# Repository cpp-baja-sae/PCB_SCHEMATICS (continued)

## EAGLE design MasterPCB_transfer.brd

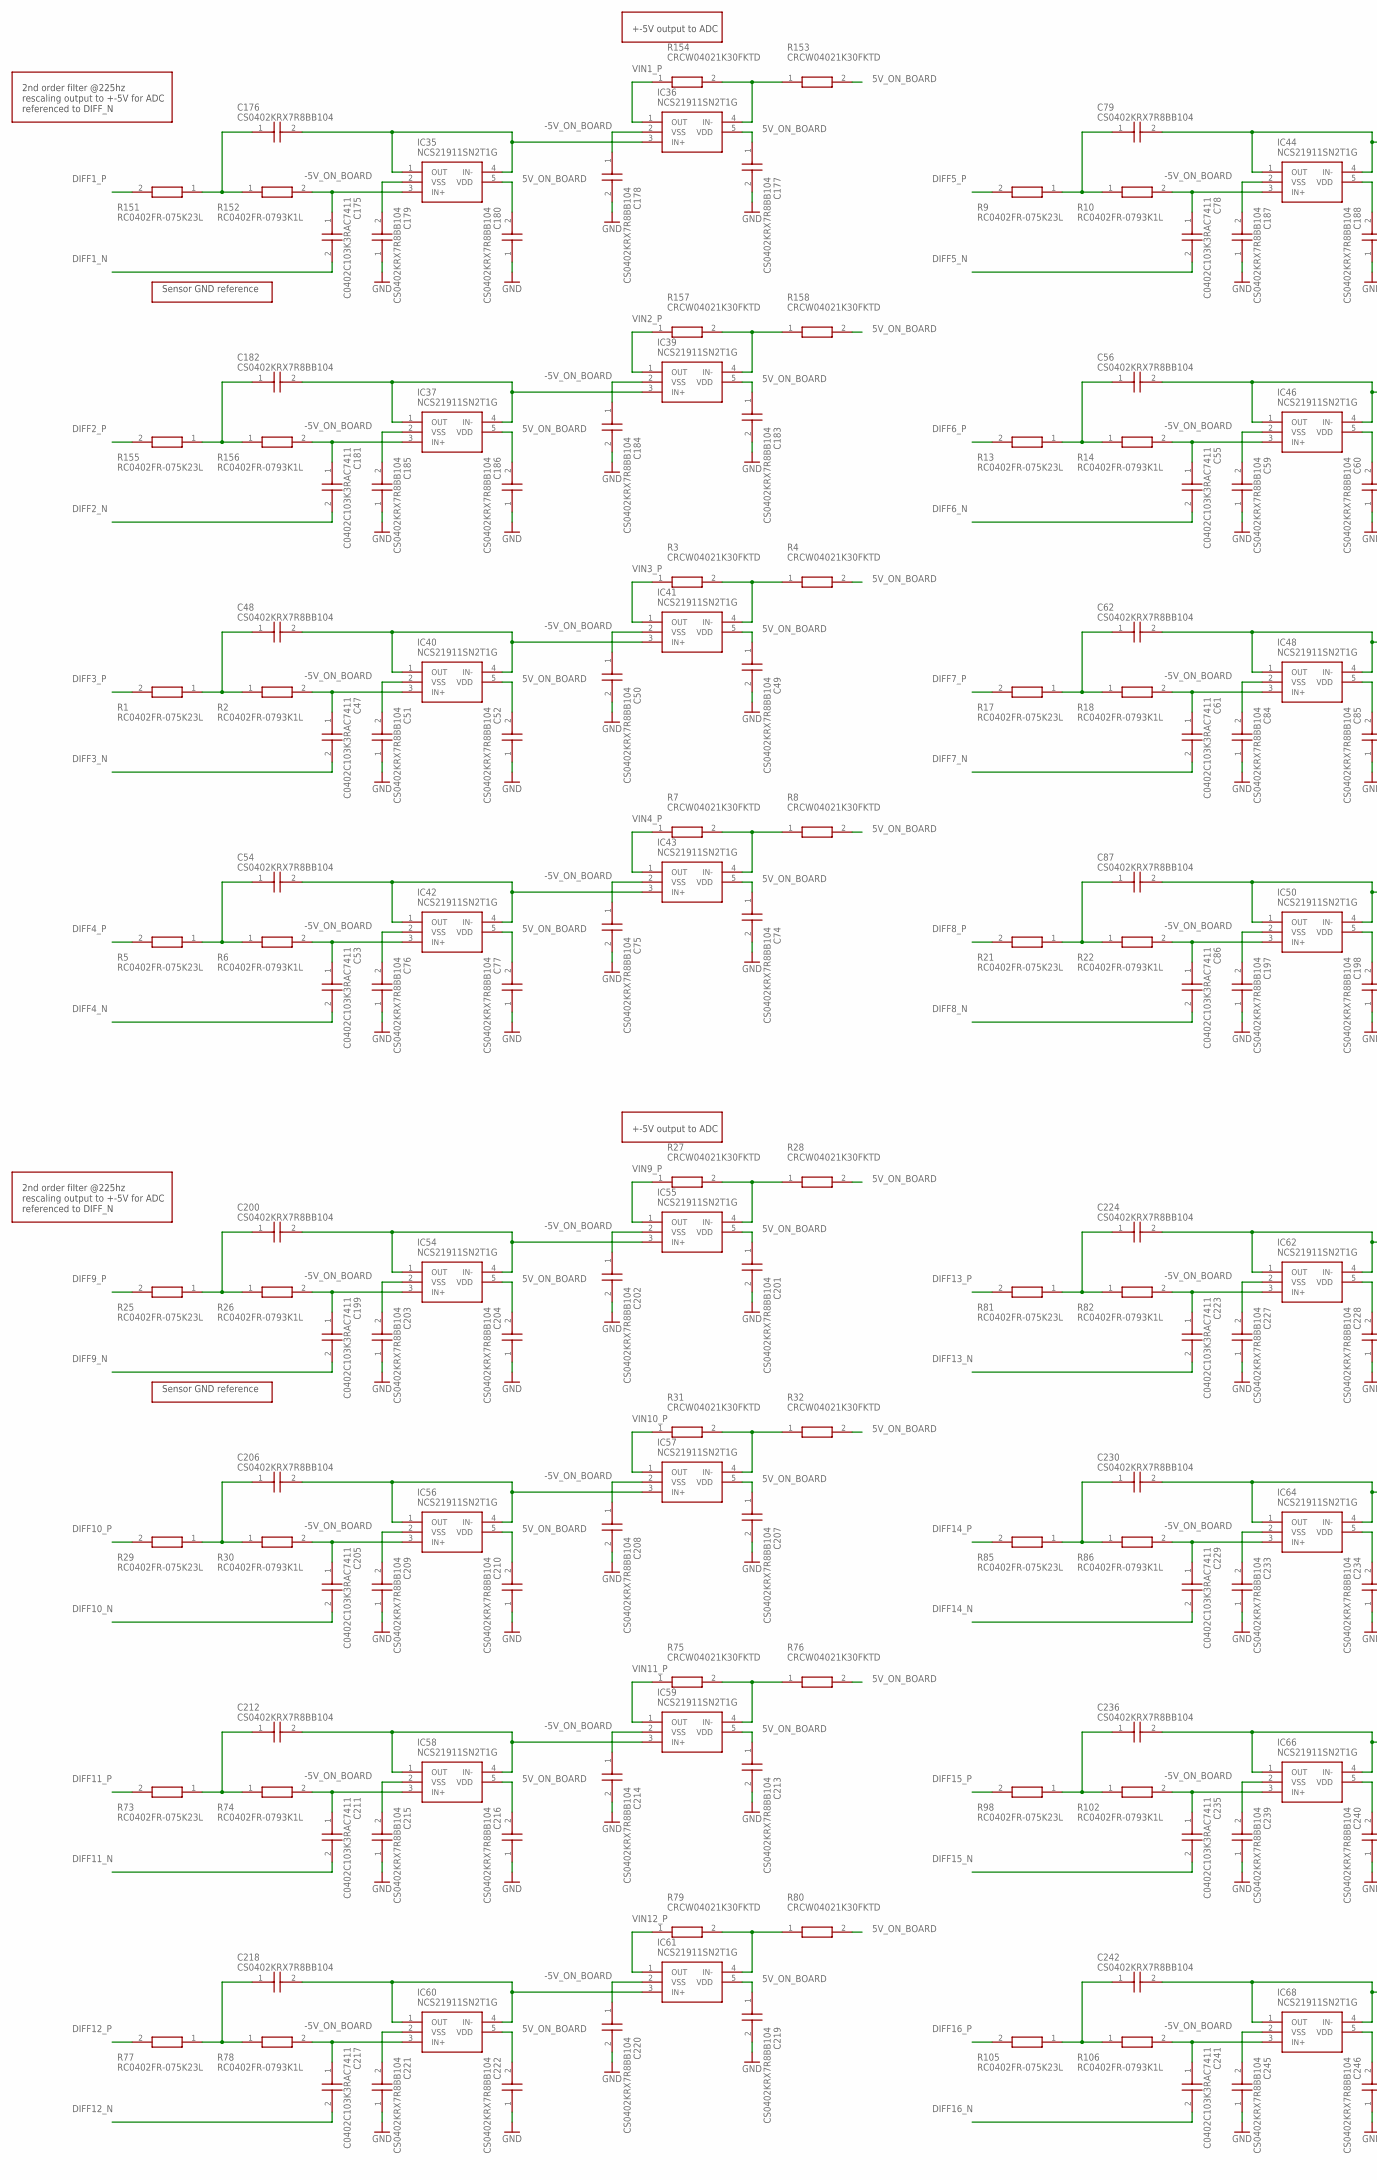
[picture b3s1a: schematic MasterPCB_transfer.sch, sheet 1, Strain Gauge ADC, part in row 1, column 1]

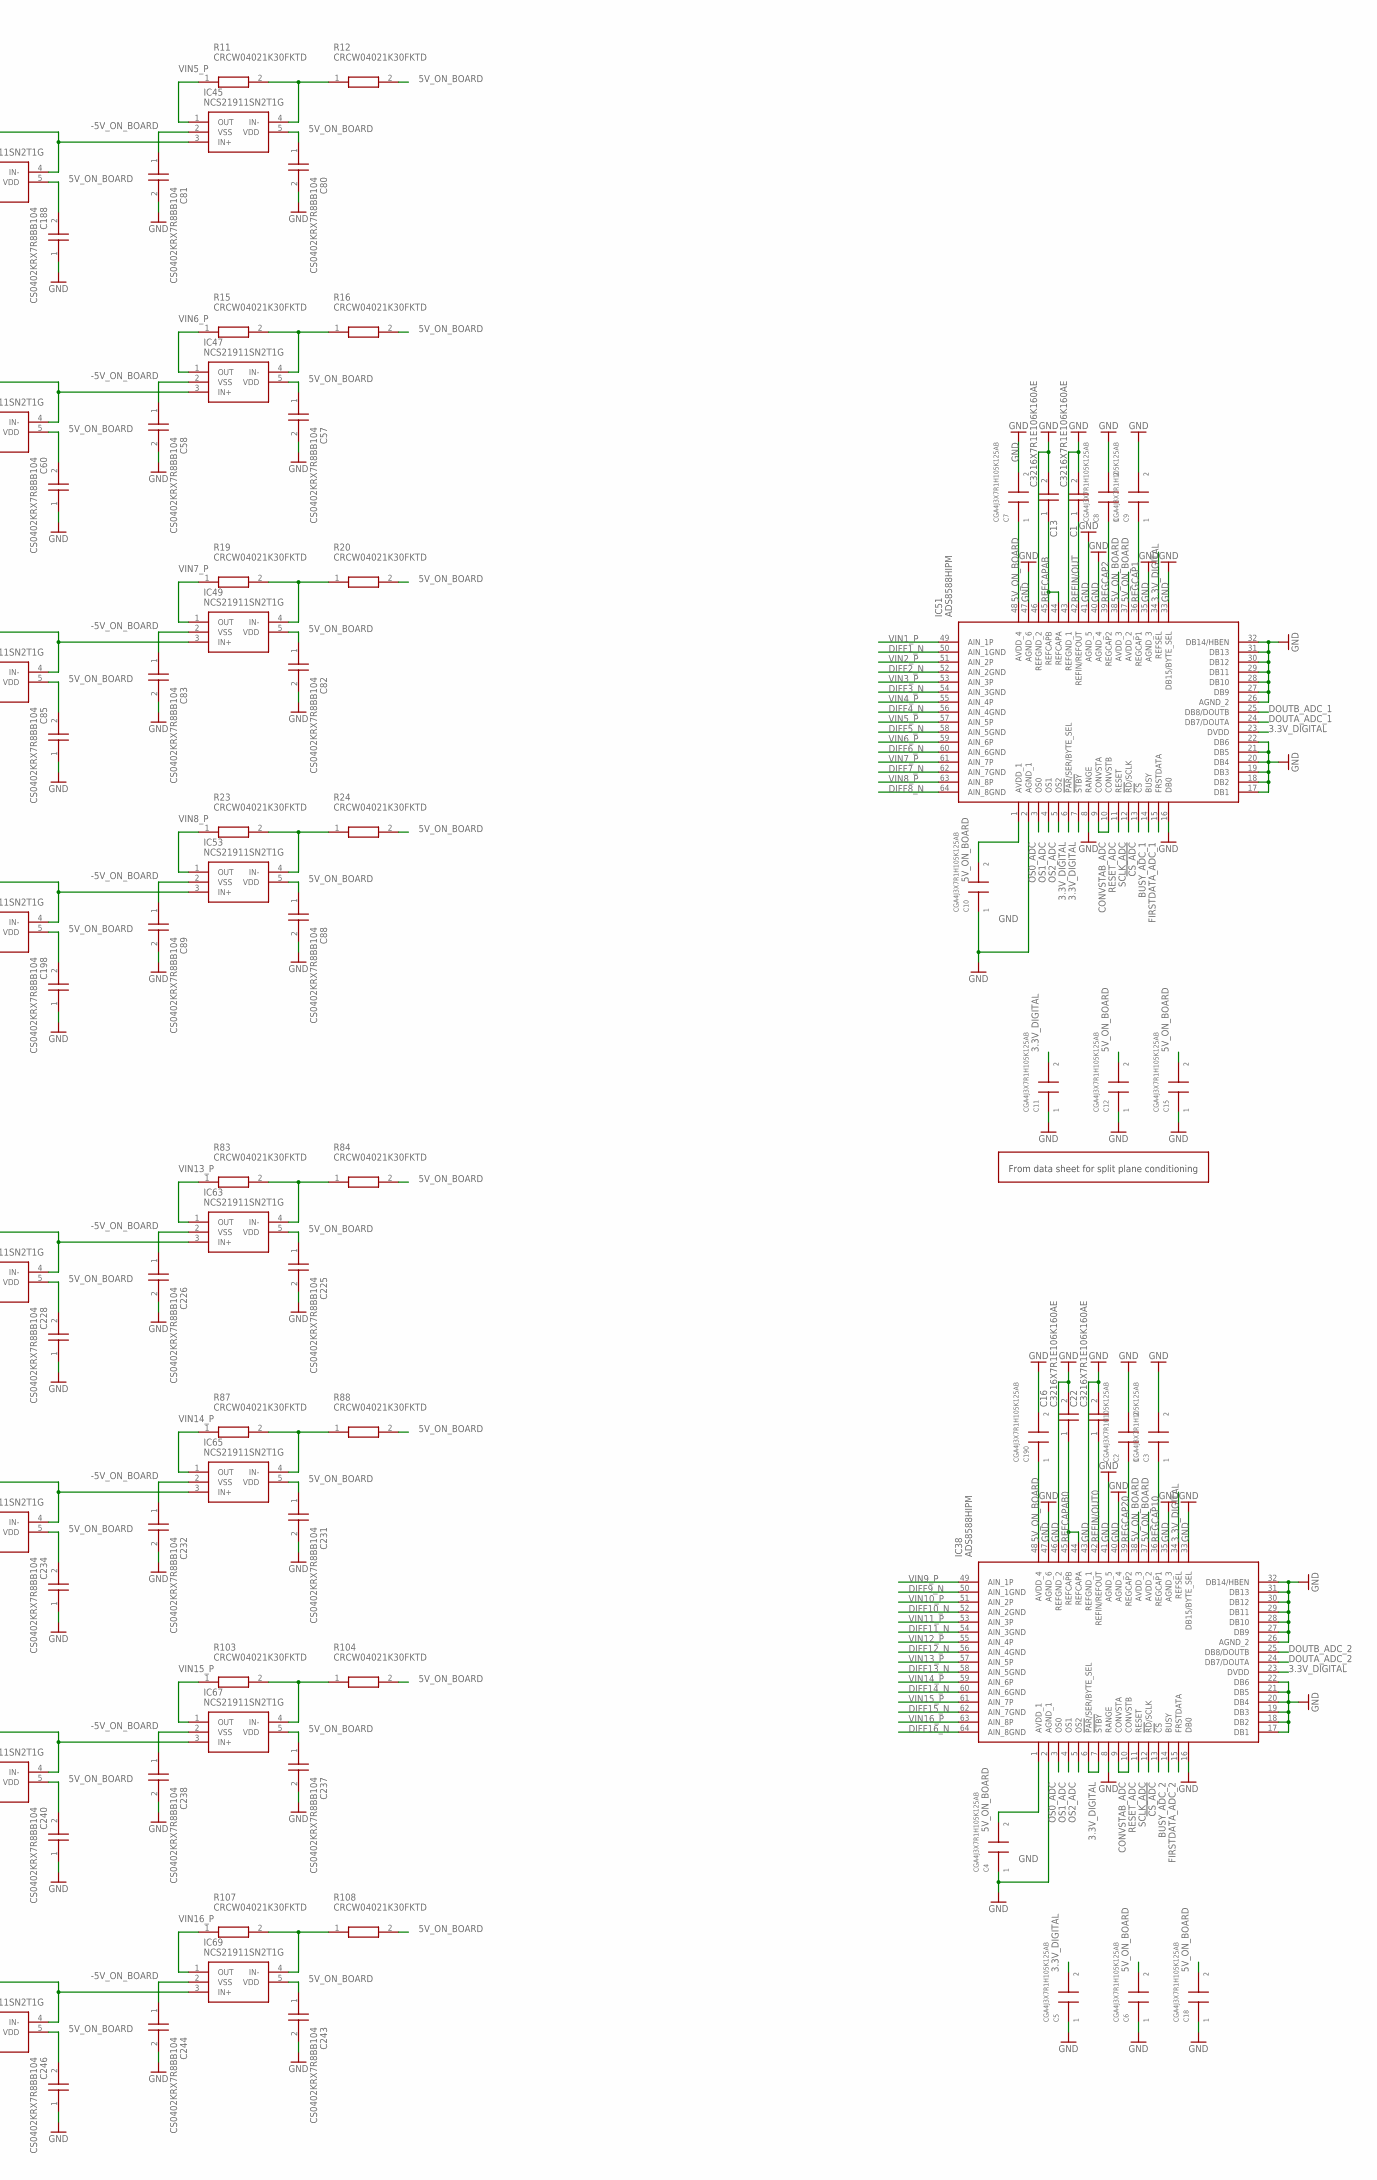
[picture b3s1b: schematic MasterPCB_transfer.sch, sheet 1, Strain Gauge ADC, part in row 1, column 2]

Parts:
C1, C13, C16, C22: C3216X7R1E106K160AE; C3216_COMMERCIAL
C2, C3, C4, C5, C6, C7, C8, C9, C10, C11, C12, C15, C18, C190: CGA4J3X7R1H105K125AB; CAPC2012X145N
C47, C53, C55, C61, C78, C86, C175, C181, C199, C205, C211, C217, C223, C229, C235, C241: C0402C103K3RAC7411; C0402
C48, C49, C50, C51, C52, C54, C56, C57, C58, C59, C60, C62, C74, C75, C76, C77, C79, C80, C81, C82, C83, C84, C85, C87, C88, C89, C176, C177, C178, C179, C180, C182, C183, C184, C185, C186, C187, C188, C197, C198, C200, C201, C202, C203, C204, C206, C207, C208, C209, C210, C212, C213, C214, C215, C216, C218, C219, C220, C221, C222, C224, C225, C226, C227, C228, C230, C231, C232, C233, C234, C236, C237, C238, C239, C240, C242, C243, C244, C245, C246: CS0402KRX7R8BB104; CAPC1005X65N
IC35, IC36, IC37, IC39, IC40, IC41, IC42, IC43, IC44, IC45, IC46, IC47, IC48, IC49, IC50, IC53, IC54, IC55, IC56, IC57, IC58, IC59, IC60, IC61, IC62, IC63, IC64, IC65, IC66, IC67, IC68, IC69: NCS21911SN2T1G; SOT95P275X110-5N
IC38, IC51: ADS8588HIPM; QFP50P1200X1200X160-64N_NO_3D
R1, R5, R9, R13, R17, R21, R25, R29, R73, R77, R81, R85, R98, R105, R151, R155: RC0402FR-075K23L; RESC1005X40N
R2, R6, R10, R14, R18, R22, R26, R30, R74, R78, R82, R86, R102, R106, R152, R156: RC0402FR-0793K1L; RESC1005X40N
R3, R4, R7, R8, R11, R12, R15, R16, R19, R20, R23, R24, R27, R28, R31, R32, R75, R76, R79, R80, R83, R84, R87, R88, R103, R104, R107, R108, R153, R154, R157, R158: CRCW04021K30FKTD; RESC1005X40N

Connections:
3.3V_DIGITAL: C5.2, C11.2, IC38.6 (!PAR!/SER/BYTE_SEL), IC38.7 (!STBY), IC38.23 (DVDD), IC38.34 (REFSEL), IC51.6 (!PAR!/SER/BYTE_SEL), IC51.7 (!STBY), IC51.23 (DVDD), IC51.34 (REFSEL); also elsewhere on the board
5V_ON_BOARD: C4.2, C6.2, C7.1, C10.2, C12.2, C15.2, C18.2, C49.1, C52.2, C57.1, C60.2, C74.1, C77.2, C80.1, C82.1, C85.2, C88.1, C177.1, C180.2, C183.1, C186.2, C188.2, C190.1, C198.2, C201.1, C204.2, C207.1, C210.2, C213.1, C216.2, C219.1, C222.2, C225.1, C228.2, C231.1, C234.2, C237.1, C240.2, C243.1, C246.2, IC35.5 (VDD), IC36.5 (VDD), IC37.5 (VDD), IC38.1 (AVDD_1), IC38.37 (AVDD_2), IC38.38 (AVDD_3), IC38.48 (AVDD_4), IC39.5 (VDD), IC40.5 (VDD), IC41.5 (VDD), IC42.5 (VDD), IC43.5 (VDD), IC44.5 (VDD), IC45.5 (VDD), IC46.5 (VDD), IC47.5 (VDD), IC48.5 (VDD), IC49.5 (VDD), IC50.5 (VDD), IC51.1 (AVDD_1), IC51.37 (AVDD_2), IC51.38 (AVDD_3), IC51.48 (AVDD_4), IC53.5 (VDD), IC54.5 (VDD), IC55.5 (VDD), IC56.5 (VDD), IC57.5 (VDD), IC58.5 (VDD), IC59.5 (VDD), IC60.5 (VDD), IC61.5 (VDD), IC62.5 (VDD), IC63.5 (VDD), IC64.5 (VDD), IC65.5 (VDD), IC66.5 (VDD), IC67.5 (VDD), IC68.5 (VDD), IC69.5 (VDD), R4.2, R8.2, R12.2, R16.2, R20.2, R24.2, R28.2, R32.2, R76.2, R80.2, R84.2, R88.2, R104.2, R108.2, R153.2, R158.2; also elsewhere on the board
!CS_ADC: IC38.13 (!CS), IC51.13 (!CS); also elsewhere on the board
-5V_ON_BOARD: C50.1, C51.2, C58.1, C59.2, C75.1, C76.2, C81.1, C83.1, C84.2, C89.1, C178.1, C179.2, C184.1, C185.2, C187.2, C197.2, C202.1, C203.2, C208.1, C209.2, C214.1, C215.2, C220.1, C221.2, C226.1, C227.2, C232.1, C233.2, C238.1, C239.2, C244.1, C245.2, IC35.2 (VSS), IC36.2 (VSS), IC37.2 (VSS), IC39.2 (VSS), IC40.2 (VSS), IC41.2 (VSS), IC42.2 (VSS), IC43.2 (VSS), IC44.2 (VSS), IC45.2 (VSS), IC46.2 (VSS), IC47.2 (VSS), IC48.2 (VSS), IC49.2 (VSS), IC50.2 (VSS), IC53.2 (VSS), IC54.2 (VSS), IC55.2 (VSS), IC56.2 (VSS), IC57.2 (VSS), IC58.2 (VSS), IC59.2 (VSS), IC60.2 (VSS), IC61.2 (VSS), IC62.2 (VSS), IC63.2 (VSS), IC64.2 (VSS), IC65.2 (VSS), IC66.2 (VSS), IC67.2 (VSS), IC68.2 (VSS), IC69.2 (VSS); also elsewhere on the board
BUSY_ADC_1: IC51.14 (BUSY); also elsewhere on the board
BUSY_ADC_2: IC38.14 (BUSY); also elsewhere on the board
CONVSTAB_ADC: IC38.9 (CONVSTA), IC38.10 (CONVSTB), IC51.9 (CONVSTA), IC51.10 (CONVSTB); also elsewhere on the board
DIFF1_N: C175.2, IC51.50 (AIN_1GND); also elsewhere on the board
DIFF1_P: R151.2; also elsewhere on the board
DIFF2_N: C181.2, IC51.52 (AIN_2GND); also elsewhere on the board
DIFF2_P: R155.2; also elsewhere on the board
DIFF3_N: C47.2, IC51.54 (AIN_3GND); also elsewhere on the board
DIFF3_P: R1.2; also elsewhere on the board
DIFF4_N: C53.2, IC51.56 (AIN_4GND); also elsewhere on the board
DIFF4_P: R5.2; also elsewhere on the board
DIFF5_N: C78.2, IC51.58 (AIN_5GND); also elsewhere on the board
DIFF5_P: R9.2; also elsewhere on the board
DIFF6_N: C55.2, IC51.60 (AIN_6GND); also elsewhere on the board
DIFF6_P: R13.2; also elsewhere on the board
DIFF7_N: C61.2, IC51.62 (AIN_7GND); also elsewhere on the board
DIFF7_P: R17.2; also elsewhere on the board
DIFF8_N: C86.2, IC51.64 (AIN_8GND); also elsewhere on the board
DIFF8_P: R21.2; also elsewhere on the board
DIFF9_N: C199.2, IC38.50 (AIN_1GND); also elsewhere on the board
DIFF9_P: R25.2; also elsewhere on the board
DIFF10_N: C205.2, IC38.52 (AIN_2GND); also elsewhere on the board
DIFF10_P: R29.2; also elsewhere on the board
DIFF11_N: C211.2, IC38.54 (AIN_3GND); also elsewhere on the board
DIFF11_P: R73.2; also elsewhere on the board
DIFF12_N: C217.2, IC38.56 (AIN_4GND); also elsewhere on the board
DIFF12_P: R77.2; also elsewhere on the board
DIFF13_N: C223.2, IC38.58 (AIN_5GND); also elsewhere on the board
DIFF13_P: R81.2; also elsewhere on the board
DIFF14_N: C229.2, IC38.60 (AIN_6GND); also elsewhere on the board
DIFF14_P: R85.2; also elsewhere on the board
DIFF15_N: C235.2, IC38.62 (AIN_7GND); also elsewhere on the board
DIFF15_P: R98.2; also elsewhere on the board
DIFF16_N: C241.2, IC38.64 (AIN_8GND); also elsewhere on the board
DIFF16_P: R105.2; also elsewhere on the board
DOUTA_ADC_1: IC51.24 (DB7/DOUTA); also elsewhere on the board
DOUTA_ADC_2: IC38.24 (DB7/DOUTA); also elsewhere on the board
DOUTB_ADC_1: IC51.25 (DB8/DOUTB); also elsewhere on the board
DOUTB_ADC_2: IC38.25 (DB8/DOUTB); also elsewhere on the board
FIRSTDATA_ADC_1: IC51.15 (FRSTDATA); also elsewhere on the board
FIRSTDATA_ADC_2: IC38.15 (FRSTDATA); also elsewhere on the board
GND: C1.2, C2.2, C3.2, C4.1, C5.1, C6.1, C7.2, C8.2, C9.2, C10.1, C11.1, C12.1, C13.2, C15.1, C16.2, C18.1, C22.2, C49.2, C50.2, C51.1, C52.1, C57.2, C58.2, C59.1, C60.1, C74.2, C75.2, C76.1, C77.1, C80.2, C81.2, C82.2, C83.2, C84.1, C85.1, C88.2, C89.2, C177.2, C178.2, C179.1, C180.1, C183.2, C184.2, C185.1, C186.1, C187.1, C188.1, C190.2, C197.1, C198.1, C201.2, C202.2, C203.1, C204.1, C207.2, C208.2, C209.1, C210.1, C213.2, C214.2, C215.1, C216.1, C219.2, C220.2, C221.1, C222.1, C225.2, C226.2, C227.1, C228.1, C231.2, C232.2, C233.1, C234.1, C237.2, C238.2, C239.1, C240.1, C243.2, C244.2, C245.1, C246.1, IC38.2 (AGND_1), IC38.8 (RANGE), IC38.16 (DB0), IC38.17 (DB1), IC38.18 (DB2), IC38.19 (DB3), IC38.20 (DB4), IC38.21 (DB5), IC38.22 (DB6), IC38.26 (AGND_2), IC38.27 (DB9), IC38.28 (DB10), IC38.29 (DB11), IC38.30 (DB12), IC38.31 (DB13), IC38.32 (DB14/HBEN), IC38.33 (DB15/BYTE_SEL), IC38.35 (AGND_3), IC38.40 (AGND_4), IC38.41 (AGND_5), IC38.43 (REFGND_1), IC38.46 (REFGND_2), IC38.47 (AGND_6), IC51.2 (AGND_1), IC51.8 (RANGE), IC51.16 (DB0), IC51.17 (DB1), IC51.18 (DB2), IC51.19 (DB3), IC51.20 (DB4), IC51.21 (DB5), IC51.22 (DB6), IC51.26 (AGND_2), IC51.27 (DB9), IC51.28 (DB10), IC51.29 (DB11), IC51.30 (DB12), IC51.31 (DB13), IC51.32 (DB14/HBEN), IC51.33 (DB15/BYTE_SEL), IC51.35 (AGND_3), IC51.40 (AGND_4), IC51.41 (AGND_5), IC51.43 (REFGND_1), IC51.46 (REFGND_2), IC51.47 (AGND_6); also elsewhere on the board
unnamed: C48.1, R1.1, R2.1
unnamed: C47.1, IC40.3 (IN+), R2.2
unnamed: IC41.4 (IN-), R3.2, R4.1
unnamed: C48.2, IC40.1 (OUT), IC40.4 (IN-), IC41.3 (IN+)
unnamed: C182.1, R155.1, R156.1
unnamed: C54.1, R5.1, R6.1
unnamed: C53.1, IC42.3 (IN+), R6.2
unnamed: IC43.4 (IN-), R7.2, R8.1
unnamed: C54.2, IC42.1 (OUT), IC42.4 (IN-), IC43.3 (IN+)
unnamed: C79.1, R9.1, R10.1
unnamed: C78.1, IC44.3 (IN+), R10.2
unnamed: IC45.4 (IN-), R11.2, R12.1
unnamed: C79.2, IC44.1 (OUT), IC44.4 (IN-), IC45.3 (IN+)
unnamed: C56.1, R13.1, R14.1
unnamed: C55.1, IC46.3 (IN+), R14.2
unnamed: IC47.4 (IN-), R15.2, R16.1
unnamed: C56.2, IC46.1 (OUT), IC46.4 (IN-), IC47.3 (IN+)
unnamed: C62.1, R17.1, R18.1
unnamed: C61.1, IC48.3 (IN+), R18.2
unnamed: IC49.4 (IN-), R19.2, R20.1
unnamed: C62.2, IC48.1 (OUT), IC48.4 (IN-), IC49.3 (IN+)
unnamed: C87.1, R21.1, R22.1
unnamed: C86.1, IC50.3 (IN+), R22.2
unnamed: IC53.4 (IN-), R23.2, R24.1
unnamed: C87.2, IC50.1 (OUT), IC50.4 (IN-), IC53.3 (IN+)
unnamed: C200.1, R25.1, R26.1
unnamed: C199.1, IC54.3 (IN+), R26.2
unnamed: IC55.4 (IN-), R27.2, R28.1
unnamed: C200.2, IC54.1 (OUT), IC54.4 (IN-), IC55.3 (IN+)
unnamed: C206.1, R29.1, R30.1
unnamed: C176.2, IC35.1 (OUT), IC35.4 (IN-), IC36.3 (IN+)
unnamed: C176.1, R151.1, R152.1
unnamed: C175.1, IC35.3 (IN+), R152.2
unnamed: IC36.4 (IN-), R153.1, R154.2
unnamed: C181.1, IC37.3 (IN+), R156.2
unnamed: IC39.4 (IN-), R157.2, R158.1
unnamed: C182.2, IC37.1 (OUT), IC37.4 (IN-), IC39.3 (IN+)
unnamed: C205.1, IC56.3 (IN+), R30.2
unnamed: IC57.4 (IN-), R31.2, R32.1
unnamed: C206.2, IC56.1 (OUT), IC56.4 (IN-), IC57.3 (IN+)
unnamed: C212.1, R73.1, R74.1
unnamed: C211.1, IC58.3 (IN+), R74.2
unnamed: IC59.4 (IN-), R75.2, R76.1
unnamed: C212.2, IC58.1 (OUT), IC58.4 (IN-), IC59.3 (IN+)
unnamed: C218.1, R77.1, R78.1
unnamed: C217.1, IC60.3 (IN+), R78.2
unnamed: IC61.4 (IN-), R79.2, R80.1
unnamed: C218.2, IC60.1 (OUT), IC60.4 (IN-), IC61.3 (IN+)
unnamed: C224.1, R81.1, R82.1
unnamed: C223.1, IC62.3 (IN+), R82.2
unnamed: IC63.4 (IN-), R83.2, R84.1
unnamed: C224.2, IC62.1 (OUT), IC62.4 (IN-), IC63.3 (IN+)
unnamed: C230.1, R85.1, R86.1
unnamed: C229.1, IC64.3 (IN+), R86.2
unnamed: IC65.4 (IN-), R87.2, R88.1
unnamed: C230.2, IC64.1 (OUT), IC64.4 (IN-), IC65.3 (IN+)
unnamed: C236.1, R98.1, R102.1
unnamed: C235.1, IC66.3 (IN+), R102.2
unnamed: IC67.4 (IN-), R103.2, R104.1
unnamed: C236.2, IC66.1 (OUT), IC66.4 (IN-), IC67.3 (IN+)
unnamed: C242.1, R105.1, R106.1
unnamed: C241.1, IC68.3 (IN+), R106.2
unnamed: IC69.4 (IN-), R107.2, R108.1
unnamed: C242.2, IC68.1 (OUT), IC68.4 (IN-), IC69.3 (IN+)
OS0_ADC: IC38.3 (OS0), IC51.3 (OS0); also elsewhere on the board
OS1_ADC: IC38.4 (OS1), IC51.4 (OS1); also elsewhere on the board
OS2_ADC: IC38.5 (OS2), IC51.5 (OS2); also elsewhere on the board
REFCAPAB: C13.1, IC51.44 (REFCAPA), IC51.45 (REFCAPB)
REFCAPAB0: C16.1, IC38.44 (REFCAPA), IC38.45 (REFCAPB)
REFIN/OUT: C1.1, IC51.42 (REFIN/REFOUT)
REFIN/OUT0: C22.1, IC38.42 (REFIN/REFOUT)
REGCAP1: C9.1, IC51.36 (REGCAP1)
REGCAP2: C8.1, IC51.39 (REGCAP2)
REGCAP10: C3.1, IC38.36 (REGCAP1)
REGCAP20: C2.1, IC38.39 (REGCAP2)
RESET_ADC: IC38.11 (RESET), IC51.11 (RESET); also elsewhere on the board
SCLK_ADC: IC38.12 (!RD!/SCLK), IC51.12 (!RD!/SCLK); also elsewhere on the board
VIN1_P: IC36.1 (OUT), IC51.49 (AIN_1P), R154.1
VIN2_P: IC39.1 (OUT), IC51.51 (AIN_2P), R157.1
VIN3_P: IC41.1 (OUT), IC51.53 (AIN_3P), R3.1
VIN4_P: IC43.1 (OUT), IC51.55 (AIN_4P), R7.1
VIN5_P: IC45.1 (OUT), IC51.57 (AIN_5P), R11.1
VIN6_P: IC47.1 (OUT), IC51.59 (AIN_6P), R15.1
VIN7_P: IC49.1 (OUT), IC51.61 (AIN_7P), R19.1
VIN8_P: IC51.63 (AIN_8P), IC53.1 (OUT), R23.1
VIN9_P: IC38.49 (AIN_1P), IC55.1 (OUT), R27.1
VIN10_P: IC38.51 (AIN_2P), IC57.1 (OUT), R31.1
VIN11_P: IC38.53 (AIN_3P), IC59.1 (OUT), R75.1
VIN12_P: IC38.55 (AIN_4P), IC61.1 (OUT), R79.1
VIN13_P: IC38.57 (AIN_5P), IC63.1 (OUT), R83.1
VIN14_P: IC38.59 (AIN_6P), IC65.1 (OUT), R87.1
VIN15_P: IC38.61 (AIN_7P), IC67.1 (OUT), R103.1
VIN16_P: IC38.63 (AIN_8P), IC69.1 (OUT), R107.1

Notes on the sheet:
From data sheet for split plane conditioning
2nd order filter @225hz rescaling output to +-5V for ADC referenced to DIFF_N
Sensor GND reference
+-5V output to ADC

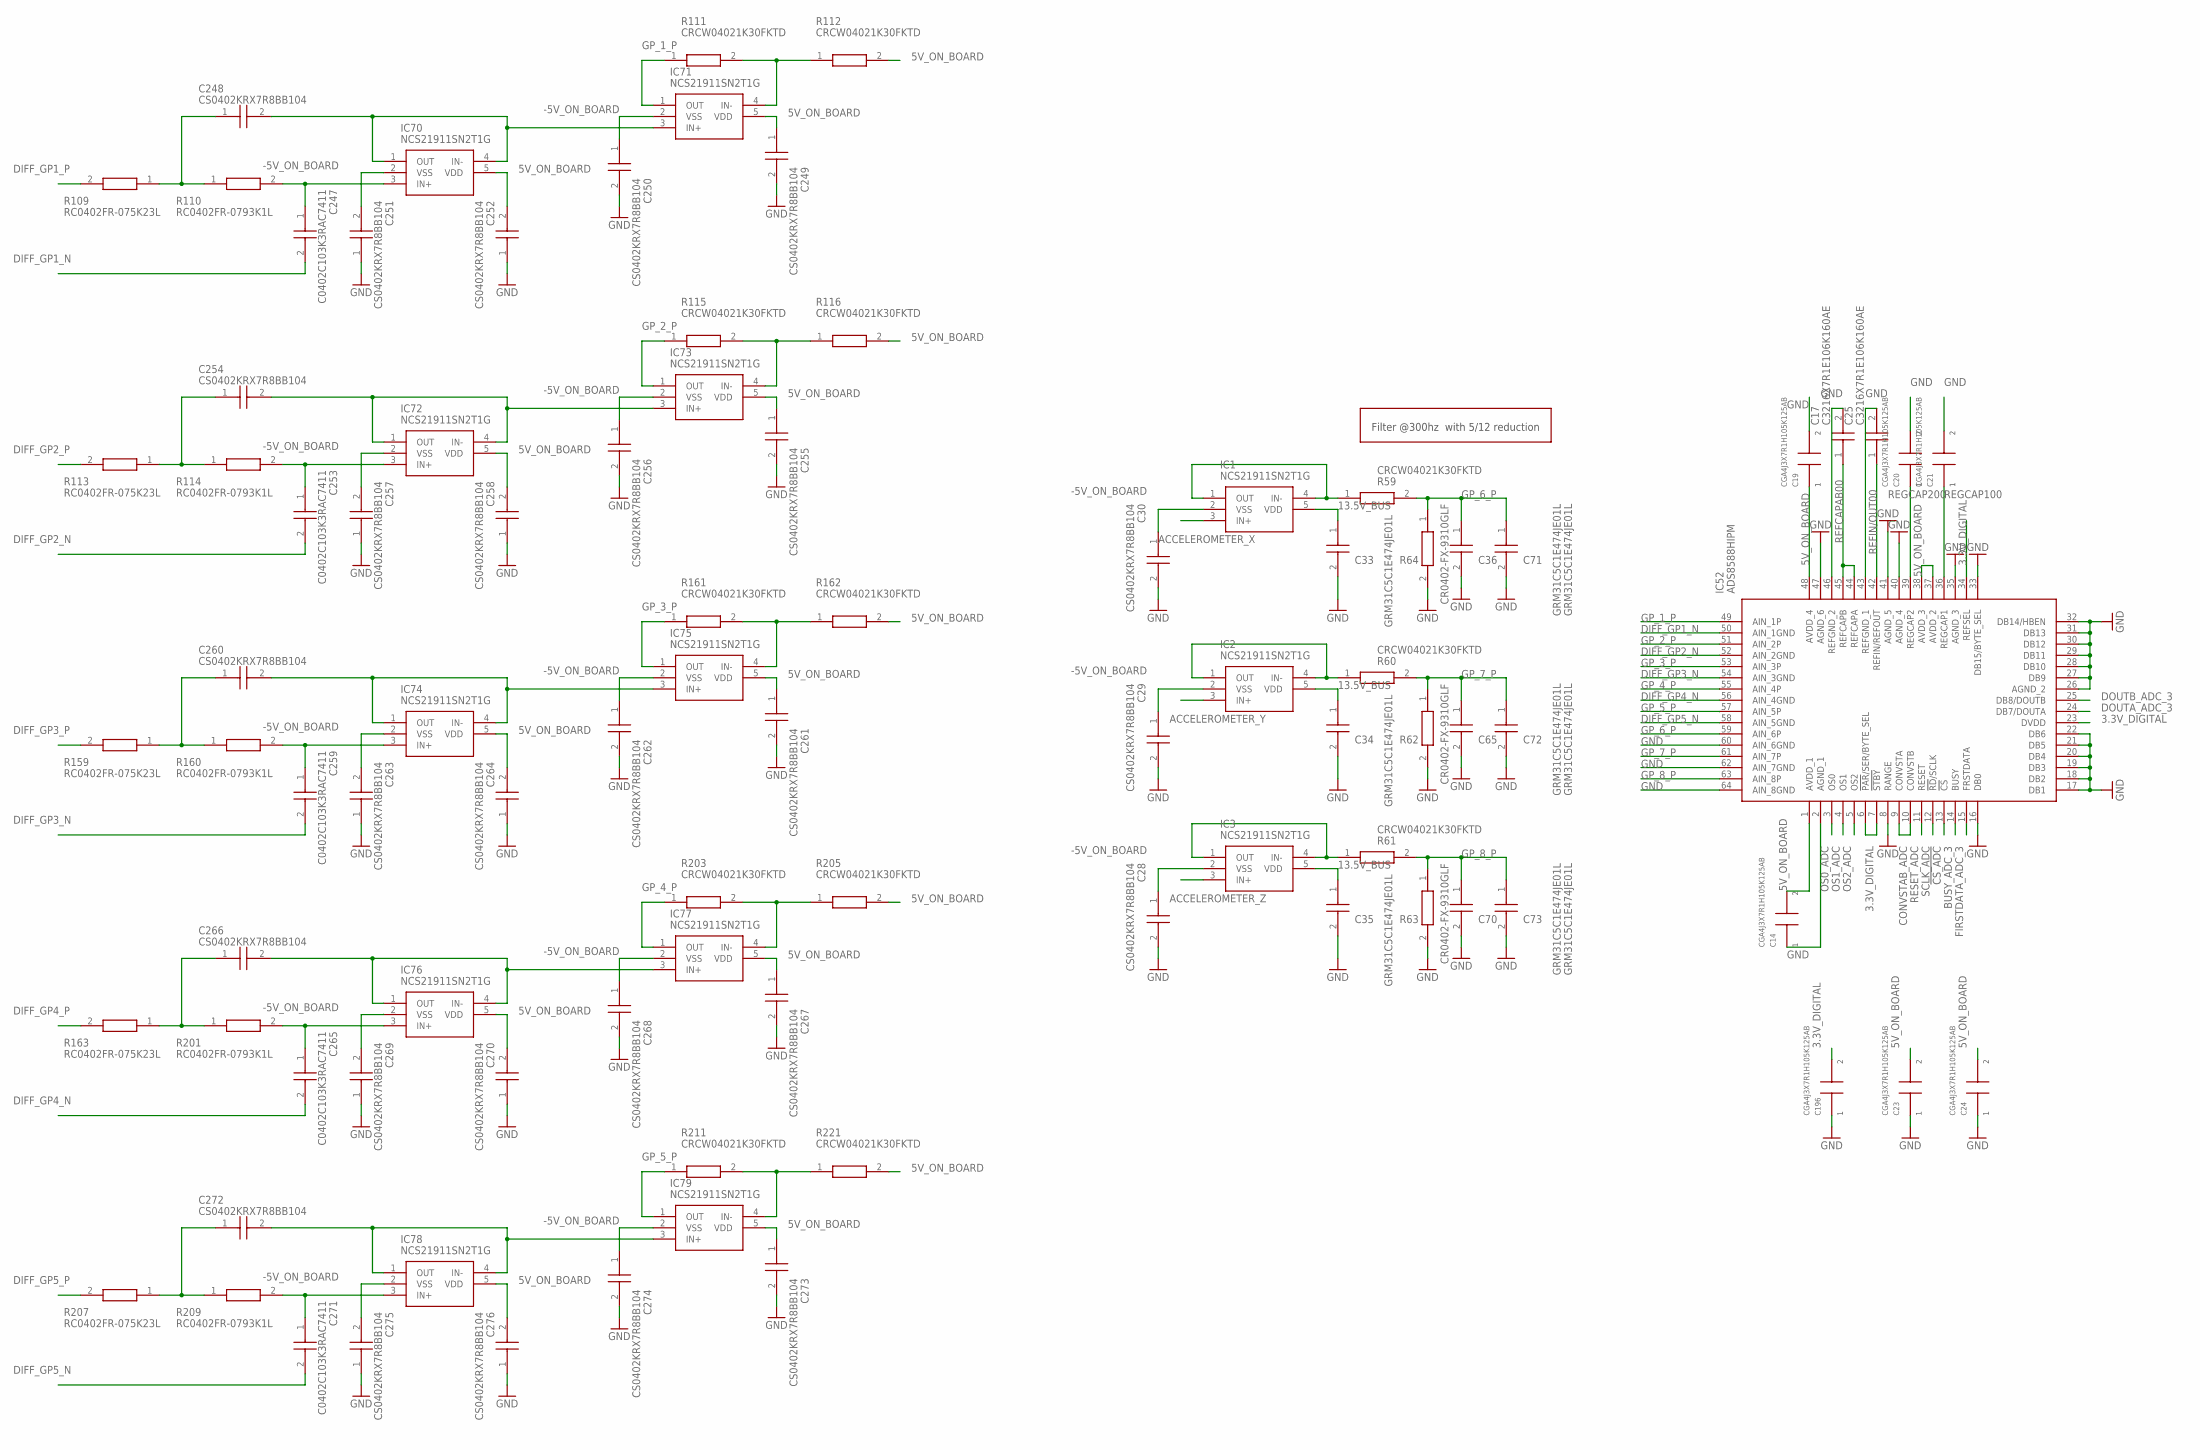
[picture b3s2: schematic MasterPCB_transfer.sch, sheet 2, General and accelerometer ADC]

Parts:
C14, C19, C20, C21, C23, C24, C196: CGA4J3X7R1H105K125AB; CAPC2012X145N
C17, C25: C3216X7R1E106K160AE; C3216_COMMERCIAL
C28, C29, C30, C248, C249, C250, C251, C252, C254, C255, C256, C257, C258, C260, C261, C262, C263, C264, C266, C267, C268, C269, C270, C272, C273, C274, C275, C276: CS0402KRX7R8BB104; CAPC1005X65N
C33, C34, C35, C36, C65, C70, C71, C72, C73: GRM31C5C1E474JE01L; CAPC3216X180N
C247, C253, C259, C265, C271: C0402C103K3RAC7411; C0402
IC1, IC2, IC3, IC70, IC71, IC72, IC73, IC74, IC75, IC76, IC77, IC78, IC79: NCS21911SN2T1G; SOT95P275X110-5N
IC52: ADS8588HIPM; QFP50P1200X1200X160-64N_NO_3D
R59, R60, R61, R111, R112, R115, R116, R161, R162, R203, R205, R211, R221: CRCW04021K30FKTD; RESC1005X40N
R62, R63, R64: CR0402-FX-9310GLF; RESC1005X40N
R109, R113, R159, R163, R207: RC0402FR-075K23L; RESC1005X40N
R110, R114, R160, R201, R209: RC0402FR-0793K1L; RESC1005X40N

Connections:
3.3V_DIGITAL: C196.2, IC52.6 (!PAR!/SER/BYTE_SEL), IC52.7 (!STBY), IC52.23 (DVDD), IC52.34 (REFSEL); also elsewhere on the board
5V_ON_BOARD: C14.2, C19.1, C23.2, C24.2, C249.1, C252.2, C255.1, C258.2, C261.1, C264.2, C267.1, C270.2, C273.1, C276.2, IC52.1 (AVDD_1), IC52.37 (AVDD_2), IC52.38 (AVDD_3), IC52.48 (AVDD_4), IC70.5 (VDD), IC71.5 (VDD), IC72.5 (VDD), IC73.5 (VDD), IC74.5 (VDD), IC75.5 (VDD), IC76.5 (VDD), IC77.5 (VDD), IC78.5 (VDD), IC79.5 (VDD), R112.2, R116.2, R162.2, R205.2, R221.2; also elsewhere on the board
13.5V_BUS: C33.1, C34.1, C35.1, IC1.5 (VDD), IC2.5 (VDD), IC3.5 (VDD); also elsewhere on the board
!CS_ADC: IC52.13 (!CS); also elsewhere on the board
-5V_ON_BOARD: C28.1, C29.1, C30.1, C250.1, C251.2, C256.1, C257.2, C262.1, C263.2, C268.1, C269.2, C274.1, C275.2, IC1.2 (VSS), IC2.2 (VSS), IC3.2 (VSS), IC70.2 (VSS), IC71.2 (VSS), IC72.2 (VSS), IC73.2 (VSS), IC74.2 (VSS), IC75.2 (VSS), IC76.2 (VSS), IC77.2 (VSS), IC78.2 (VSS), IC79.2 (VSS); also elsewhere on the board
ACCELEROMETER_X: IC1.3 (IN+); also elsewhere on the board
ACCELEROMETER_Y: IC2.3 (IN+); also elsewhere on the board
ACCELEROMETER_Z: IC3.3 (IN+); also elsewhere on the board
BUSY_ADC_3: IC52.14 (BUSY); also elsewhere on the board
CONVSTAB_ADC: IC52.9 (CONVSTA), IC52.10 (CONVSTB); also elsewhere on the board
DIFF_GP1_N: C247.2, IC52.50 (AIN_1GND); also elsewhere on the board
DIFF_GP1_P: R109.2; also elsewhere on the board
DIFF_GP2_N: C253.2, IC52.52 (AIN_2GND); also elsewhere on the board
DIFF_GP2_P: R113.2; also elsewhere on the board
DIFF_GP3_N: C259.2, IC52.54 (AIN_3GND); also elsewhere on the board
DIFF_GP3_P: R159.2; also elsewhere on the board
DIFF_GP4_N: C265.2, IC52.56 (AIN_4GND); also elsewhere on the board
DIFF_GP4_P: R163.2; also elsewhere on the board
DIFF_GP5_N: C271.2, IC52.58 (AIN_5GND); also elsewhere on the board
DIFF_GP5_P: R207.2; also elsewhere on the board
DOUTA_ADC_3: IC52.24 (DB7/DOUTA); also elsewhere on the board
DOUTB_ADC_3: IC52.25 (DB8/DOUTB); also elsewhere on the board
FIRSTDATA_ADC_3: IC52.15 (FRSTDATA); also elsewhere on the board
GND: C14.1, C17.2, C19.2, C20.2, C21.2, C23.1, C24.1, C25.2, C28.2, C29.2, C30.2, C33.2, C34.2, C35.2, C36.2, C65.2, C70.2, C71.2, C72.2, C73.2, C196.1, C249.2, C250.2, C251.1, C252.1, C255.2, C256.2, C257.1, C258.1, C261.2, C262.2, C263.1, C264.1, C267.2, C268.2, C269.1, C270.1, C273.2, C274.2, C275.1, C276.1, IC52.2 (AGND_1), IC52.8 (RANGE), IC52.16 (DB0), IC52.17 (DB1), IC52.18 (DB2), IC52.19 (DB3), IC52.20 (DB4), IC52.21 (DB5), IC52.22 (DB6), IC52.26 (AGND_2), IC52.27 (DB9), IC52.28 (DB10), IC52.29 (DB11), IC52.30 (DB12), IC52.31 (DB13), IC52.32 (DB14/HBEN), IC52.33 (DB15/BYTE_SEL), IC52.35 (AGND_3), IC52.40 (AGND_4), IC52.41 (AGND_5), IC52.43 (REFGND_1), IC52.46 (REFGND_2), IC52.47 (AGND_6), IC52.60 (AIN_6GND), IC52.62 (AIN_7GND), IC52.64 (AIN_8GND), R62.2, R63.2, R64.2; also elsewhere on the board
GP_1_P: IC52.49 (AIN_1P), IC71.1 (OUT), R111.1
GP_2_P: IC52.51 (AIN_2P), IC73.1 (OUT), R115.1
GP_3_P: IC52.53 (AIN_3P), IC75.1 (OUT), R161.1
GP_4_P: IC52.55 (AIN_4P), IC77.1 (OUT), R203.1
GP_5_P: IC52.57 (AIN_5P), IC79.1 (OUT), R211.1
GP_6_P: C36.1, C71.1, IC52.59 (AIN_6P), R59.2, R64.1
GP_7_P: C65.1, C72.1, IC52.61 (AIN_7P), R60.2, R62.1
GP_8_P: C70.1, C73.1, IC52.63 (AIN_8P), R61.2, R63.1
unnamed: IC1.1 (OUT), IC1.4 (IN-), R59.1
unnamed: IC3.1 (OUT), IC3.4 (IN-), R61.1
unnamed: IC2.1 (OUT), IC2.4 (IN-), R60.1
unnamed: C248.1, R109.1, R110.1
unnamed: C247.1, IC70.3 (IN+), R110.2
unnamed: IC71.4 (IN-), R111.2, R112.1
unnamed: C248.2, IC70.1 (OUT), IC70.4 (IN-), IC71.3 (IN+)
unnamed: C254.1, R113.1, R114.1
unnamed: C253.1, IC72.3 (IN+), R114.2
unnamed: IC73.4 (IN-), R115.2, R116.1
unnamed: C254.2, IC72.1 (OUT), IC72.4 (IN-), IC73.3 (IN+)
unnamed: C260.1, R159.1, R160.1
unnamed: C259.1, IC74.3 (IN+), R160.2
unnamed: IC75.4 (IN-), R161.2, R162.1
unnamed: C260.2, IC74.1 (OUT), IC74.4 (IN-), IC75.3 (IN+)
unnamed: C266.1, R163.1, R201.1
unnamed: C265.1, IC76.3 (IN+), R201.2
unnamed: IC77.4 (IN-), R203.2, R205.1
unnamed: C266.2, IC76.1 (OUT), IC76.4 (IN-), IC77.3 (IN+)
unnamed: C272.1, R207.1, R209.1
unnamed: C271.1, IC78.3 (IN+), R209.2
unnamed: IC79.4 (IN-), R211.2, R221.1
unnamed: C272.2, IC78.1 (OUT), IC78.4 (IN-), IC79.3 (IN+)
OS0_ADC: IC52.3 (OS0); also elsewhere on the board
OS1_ADC: IC52.4 (OS1); also elsewhere on the board
OS2_ADC: IC52.5 (OS2); also elsewhere on the board
REFCAPAB00: C17.1, IC52.44 (REFCAPA), IC52.45 (REFCAPB)
REFIN/OUT00: C25.1, IC52.42 (REFIN/REFOUT)
REGCAP100: C21.1, IC52.36 (REGCAP1)
REGCAP200: C20.1, IC52.39 (REGCAP2)
RESET_ADC: IC52.11 (RESET); also elsewhere on the board
SCLK_ADC: IC52.12 (!RD!/SCLK); also elsewhere on the board

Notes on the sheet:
Filter @300hz with 5/12 reduction
